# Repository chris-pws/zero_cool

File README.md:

# ZeroCool

Given that the Orange Pi Zero gets very hot when using all four cores and on-board wifi for any sustained period of time, I decided to create a fan controller that minimizes fan noise and respects the integrity of the wireless signal with respect to EMF noise. In keeping with the compact form factor of the Zero, this board shall mate securely with the SBC and cooling fan, and provide ready access to the H2+'s additional USB ports.

## Project notes

[Initial mechanical measurement and layout notes](https://github.com/cms-/zero_cool/blob/master/003.jpg)

[Rev B assembly and bring-up](https://github.com/cms-/zero_cool/blob/master/IMG_20180520_031025.jpg)

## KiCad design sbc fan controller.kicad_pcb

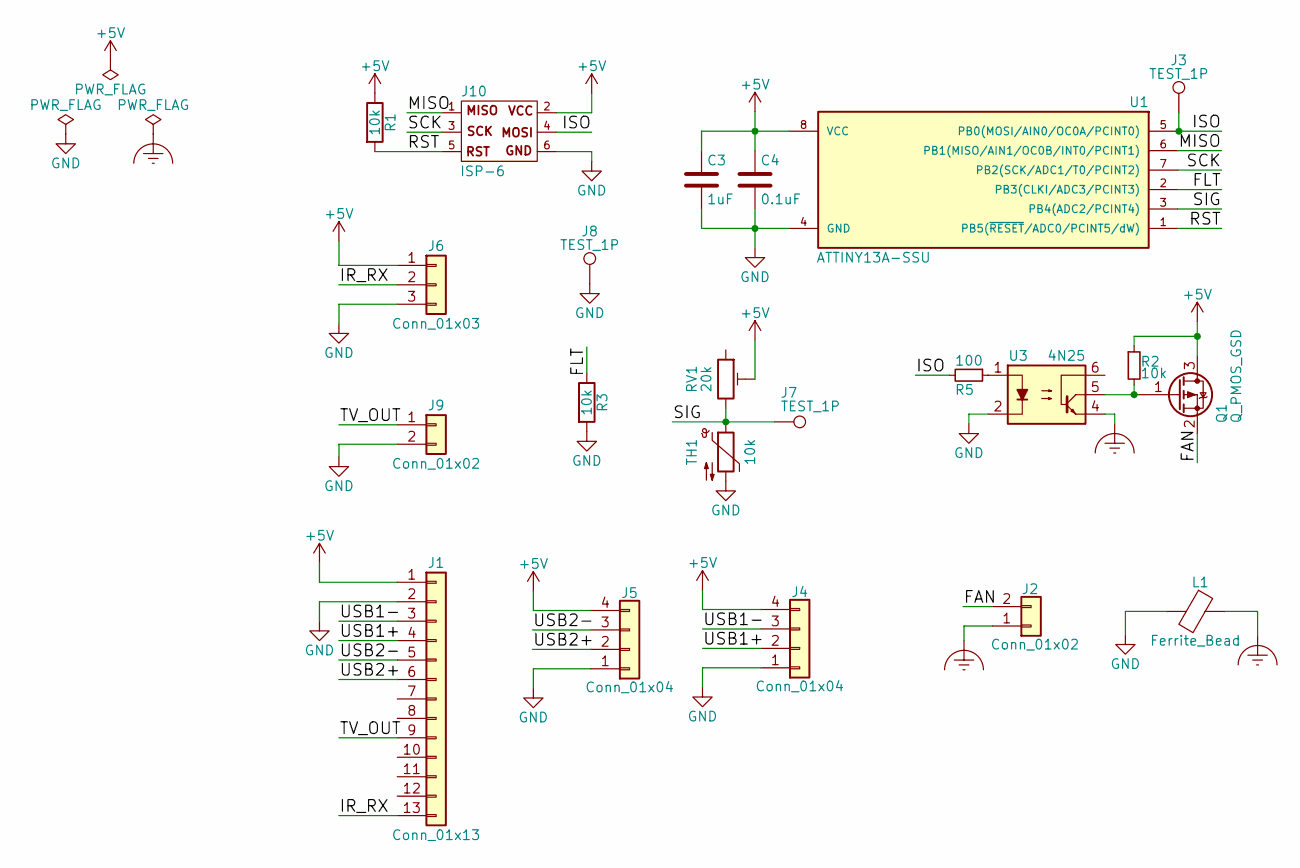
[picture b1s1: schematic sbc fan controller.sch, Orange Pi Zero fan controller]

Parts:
C3: 1uF; C_0603
C4: 0.1uF; C_0603
J1: Conn_01x13; Pin_Header_Straight_1x13_Pitch2.54mm
J2, J9: Conn_01x02; JST_ZH_SM02B-ZRSS-TB_1x02_P1.50mm_Horizontal
J3, J7, J8: TEST_1P; Measurement_Point_Round-SMD-Pad_Small
J4, J5: Conn_01x04; JST_ZH_SM04B-ZRSS-TB_1x04_P1.50mm_Horizontal
J6: Conn_01x03; JST_ZH_SM03B-ZRSS-TB_1x03_P1.50mm_Horizontal
J10: ISP-6; Pin_Header_Straight_2x03_Pitch2.54mm
L1: Ferrite_Bead; R_0805
Q1: Q_PMOS_GSD; SOT-23
R1, R2, R3: 10k; R_0805
R5: 100; R_0805
RV1: 20k; TC33
TH1: 10k; JST_ZH_SM02B-ZRSS-TB_1x02_P1.50mm_Horizontal
U1: ATTINY13A-SSU; SOIC-8_3.9x4.9mm_Pitch1.27mm
U3: 4N25; SO-6_4.4x3.6mm_Pitch1.27mm

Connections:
+5V: C3.1, C4.1, J1.1, J4.4, J5.4, J6.1, J10.2, Q1.3 (D), R1.1, R2.1, RV1.2, U1.8 (VCC)
/FAN: J2.2, Q1.2 (S)
/FLT: R3.1, U1.2 (PB3(CLKI/ADC3/PCINT3))
/IR_RX: J1.13, J6.2
/ISO: J3.1, J10.4, R5.2, U1.5 (PB0(MOSI/AIN0/OC0A/PCINT0))
/MISO: J10.1, U1.6 (PB1(MISO/AIN1/OC0B/INT0/PCINT1))
/RST: J10.5, R1.2, U1.1 (PB5(~RESET~/ADC0/PCINT5/dW))
/SCK: J10.3, U1.7 (PB2(SCK/ADC1/T0/PCINT2))
/SIG: J7.1, RV1.3, TH1.1, U1.3 (PB4(ADC2/PCINT4))
/TV_OUT: J1.9, J9.1
/USB1+: J1.4, J4.2
/USB1-: J1.3, J4.3
/USB2+: J1.6, J5.2
/USB2-: J1.5, J5.3
Earth_Clean: J2.1, L1.1, U3.4
GND: C3.2, C4.2, J1.2, J4.1, J5.1, J6.3, J8.1, J9.2, J10.6, L1.2, R3.2, TH1.2, U1.4 (GND), U3.2
unnamed: Q1.1 (G), R2.2, U3.5
unnamed: R5.1, U3.1

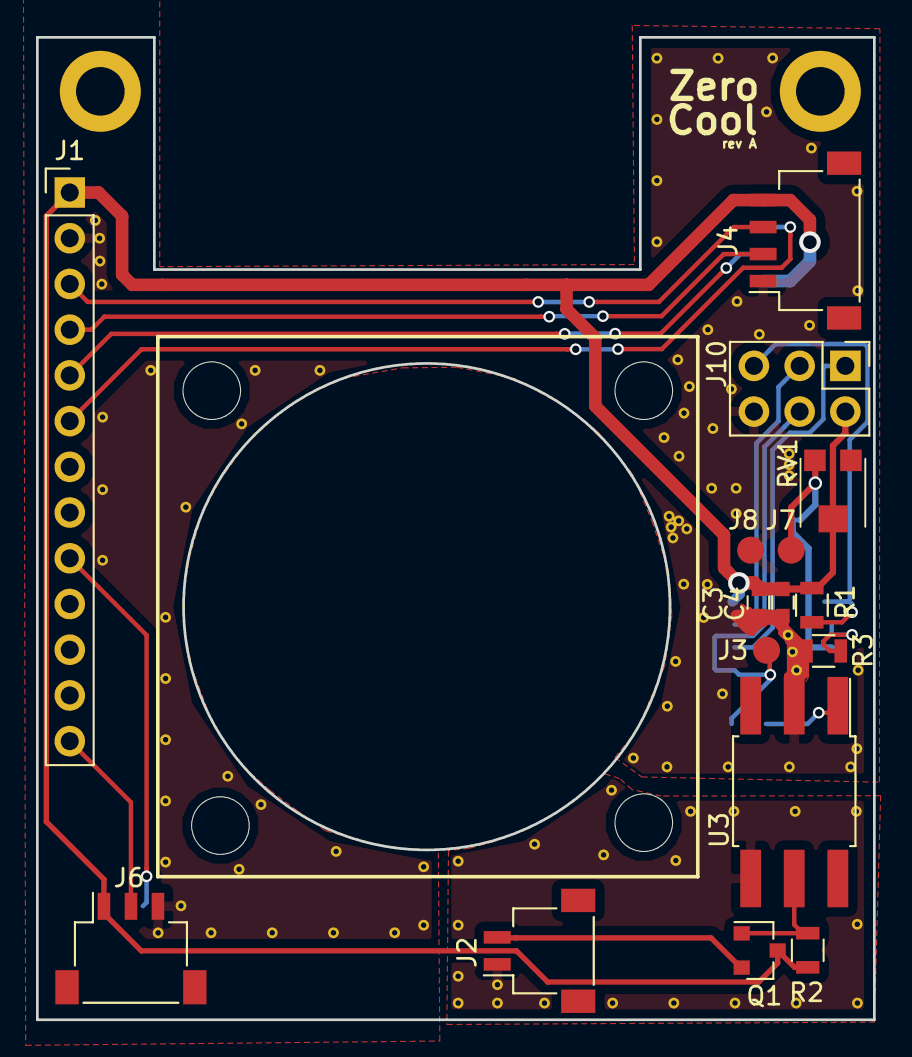
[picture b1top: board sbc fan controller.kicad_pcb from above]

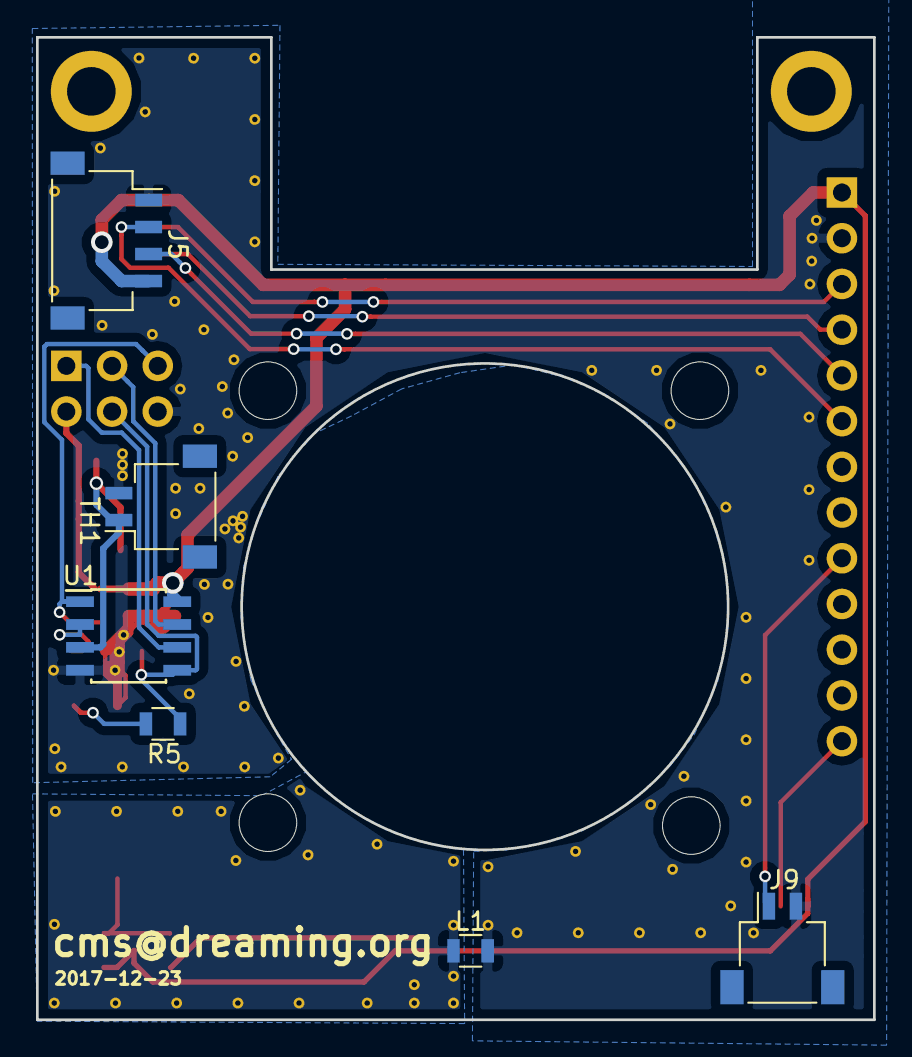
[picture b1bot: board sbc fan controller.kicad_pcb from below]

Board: 2 copper layers, 46.5 x 54.6 mm, 22 parts (6 on the bottom side), 18 nets.

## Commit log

2017-12-14 Update schematic PDF
2017-12-14 Auto stash before merge of "master" and "opi_zero_fan_controller/master"
2017-12-14 Correcting references for consistency
    Also added RCA coax connector, although this may not fit on the final board.
2017-12-14 Corrected non-inverting signal input network names
2017-12-14 Minor layout corrections
2017-12-15 Initial layout of devices
2017-12-18 Simplified design, dropped amp; added isolated ground
    After testing the dual amp circuit against a simple voltage divider, ADC yields enough resolution to discern heat levels in order to accommodate a look up table for fan speed. Isolated ground plane f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
2017-12-18 .gitignore
2017-12-24 Final layout
    Simplified layout and tested each footprint with a hard copy layout actual parts.
2017-12-28 Final schematic
2017-12-28 Final schematic update
    Reflects simplification of analog portion
2018-05-20 Rev B bring-up and testing
    Tested OK. Functions as suspected. PWM frequency needs to be lowered outside of human hearing.
2018-05-21 Mechanical measurement notes
2018-05-21 Added project notes

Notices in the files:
sbc fan controller.sch:
Released under MIT License
